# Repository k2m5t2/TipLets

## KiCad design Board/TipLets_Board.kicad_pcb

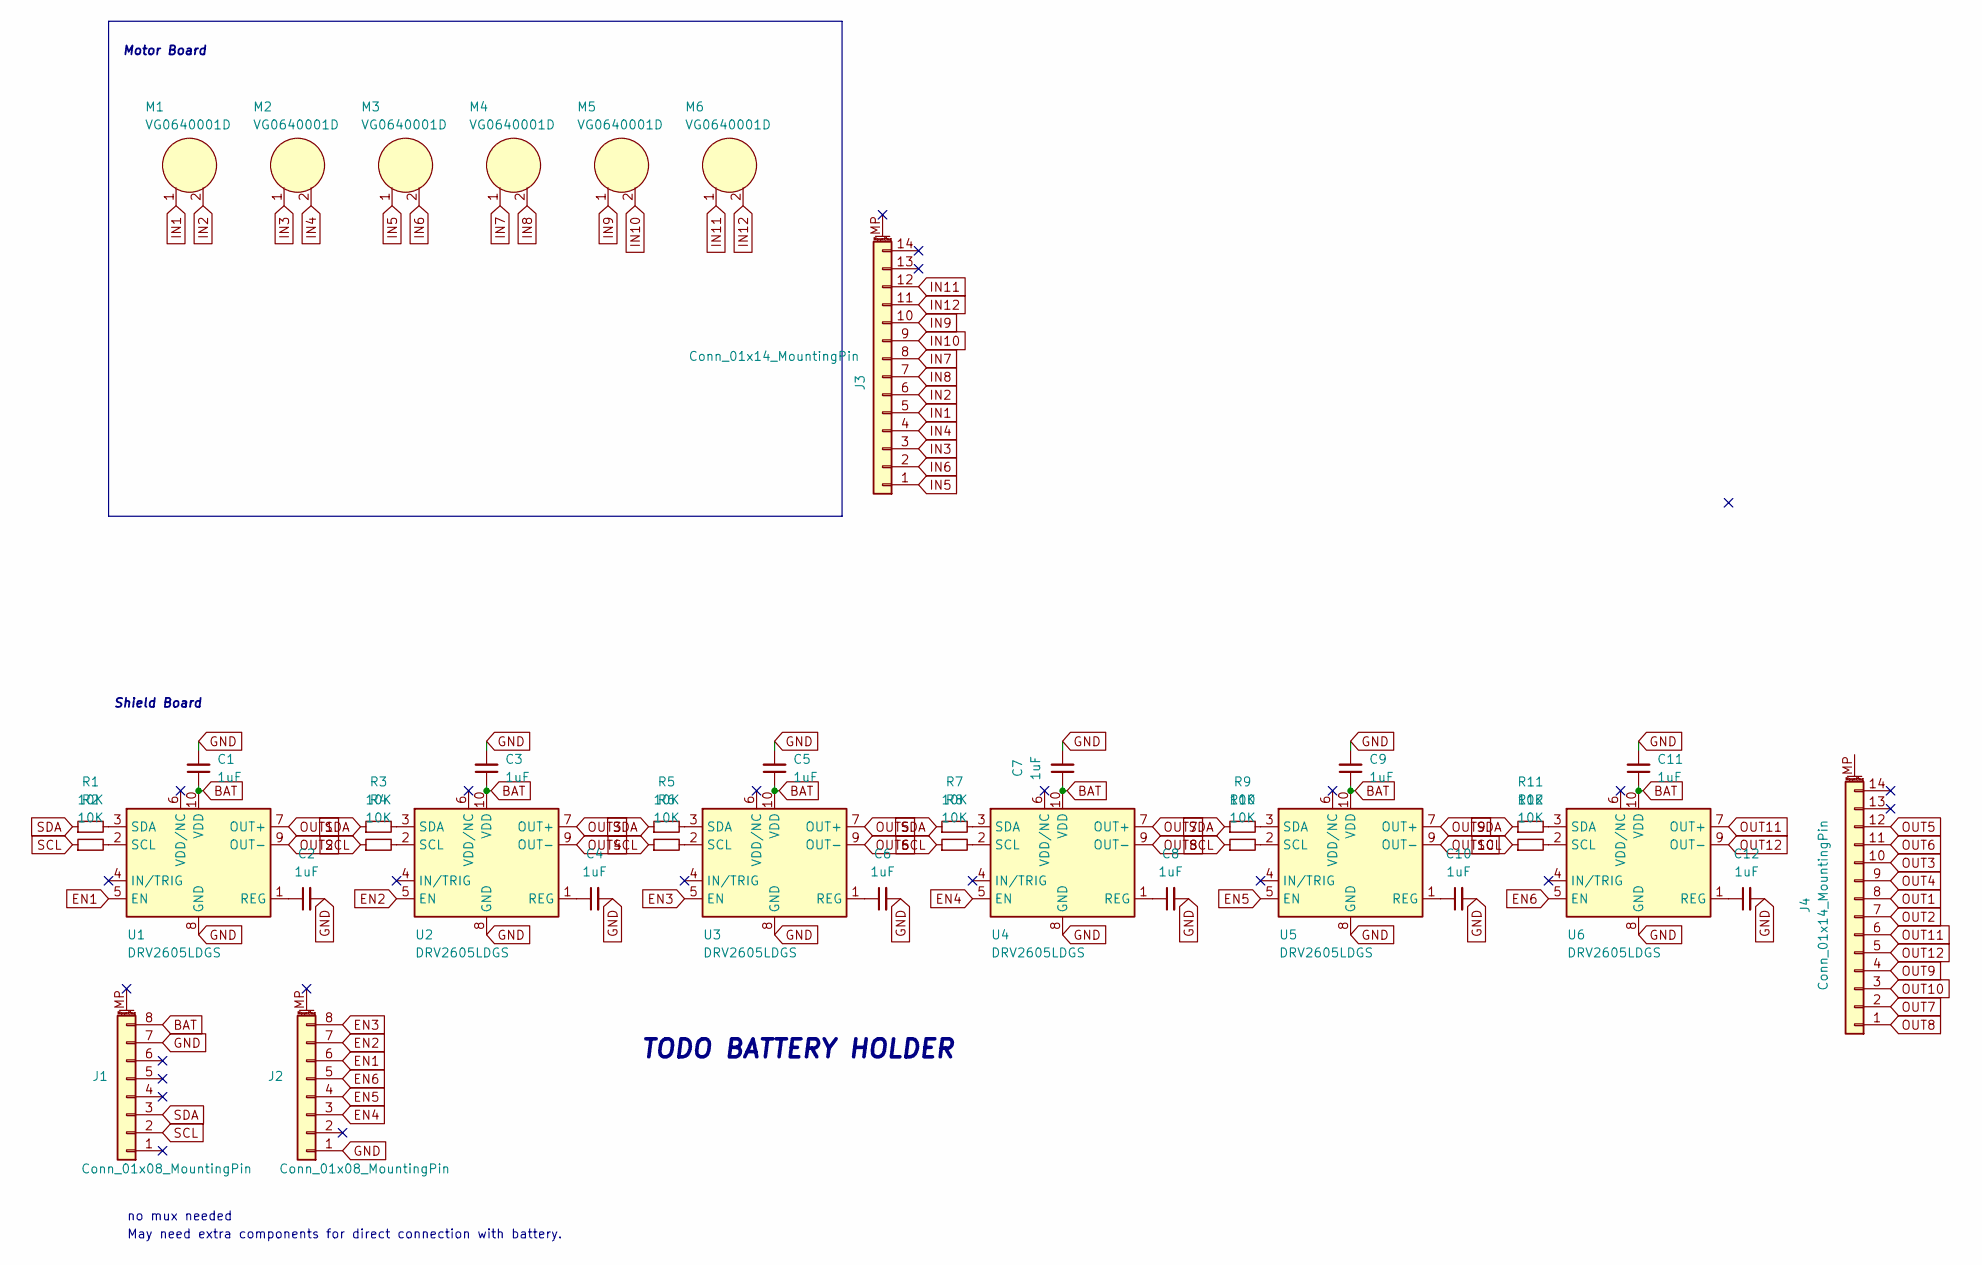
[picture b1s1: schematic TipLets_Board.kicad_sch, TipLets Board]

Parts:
C1, C2, C3, C4, C5, C6, C7, C8, C9, C10, C11, C12: 1uF; C_0402_1005Metric
J1, J2: Conn_01x08_MountingPin; PinHeader_1x08_P2.54mm_Vertical
J3, J4: Conn_01x14_MountingPin; PinHeader_2x07_P2.00mm_Vertical
M1, M2, M3, M4, M5, M6: VG0640001D
R1, R2, R3, R4, R5, R6, R7, R8, R9, R10, R11, R12: 10K; R_0402_1005Metric
U1, U2, U3, U4, U5, U6: DRV2605LDGS; VSSOP-10_3x3mm_P0.5mm

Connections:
BAT: C1.1, C3.1, C5.1, C7.1, C9.1, C11.1, J1.8, J2.2, U1.10 (VDD), U2.10 (VDD), U3.10 (VDD), U4.10 (VDD), U5.10 (VDD), U6.10 (VDD); also elsewhere on the board
EN1: J2.6, U1.5 (EN)
EN2: J2.7, U2.5 (EN)
EN3: J2.8, U3.5 (EN)
EN4: J2.3, U4.5 (EN)
EN5: J2.4, U5.5 (EN)
EN6: J2.5, U6.5 (EN)
GND: C1.2, C2.2, C3.2, C4.2, C5.2, C6.2, C7.2, C8.2, C9.2, C10.2, C11.2, C12.2, J1.7, J2.1, U1.8 (GND), U2.8 (GND), U3.8 (GND), U4.8 (GND), U5.8 (GND), U6.8 (GND); also elsewhere on the board
IN1: J3.5, M1.1
IN2: J3.6, M1.2
IN3: J3.3, M2.1
IN4: J3.4, M2.2
IN5: J3.1, M3.1
IN6: J3.2, M3.2
IN7: J3.8, M4.1
IN8: J3.7, M4.2
IN9: J3.10, M5.1
IN10: J3.9, M5.2
IN11: J3.12, M6.1
IN12: J3.11, M6.2
unnamed: C2.1, U1.1 (REG)
unnamed: C4.1, U2.1 (REG)
unnamed: C6.1, U3.1 (REG)
unnamed: C8.1, U4.1 (REG)
unnamed: C10.1, U5.1 (REG)
unnamed: C12.1, U6.1 (REG)
unnamed: R1.2, U1.3 (SDA)
unnamed: R2.2, U1.2 (SCL)
unnamed: R3.2, U2.3 (SDA)
unnamed: R4.2, U2.2 (SCL)
unnamed: R5.2, U3.3 (SDA)
unnamed: R6.2, U3.2 (SCL)
unnamed: R7.2, U4.3 (SDA)
unnamed: R8.2, U4.2 (SCL)
unnamed: R9.2, U5.3 (SDA)
unnamed: R10.2, U5.2 (SCL)
unnamed: R11.2, U6.3 (SDA)
unnamed: R12.2, U6.2 (SCL)
OUT1: J4.8, U1.7 (OUT+)
OUT2: J4.7, U1.9 (OUT-)
OUT3: J4.10, U2.7 (OUT+)
OUT4: J4.9, U2.9 (OUT-)
OUT5: J4.12, U3.7 (OUT+)
OUT6: J4.11, U3.9 (OUT-)
OUT7: J4.2, U4.7 (OUT+)
OUT8: J4.1, U4.9 (OUT-)
OUT9: J4.4, U5.7 (OUT+)
OUT10: J4.3, U5.9 (OUT-)
OUT11: J4.6, U6.7 (OUT+)
OUT12: J4.5, U6.9 (OUT-)
SCL: J1.2, R2.1, R4.1, R6.1, R8.1, R10.1, R12.1
SDA: J1.3, R1.1, R3.1, R5.1, R7.1, R9.1, R11.1

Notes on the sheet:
Motor Board
TODO BATTERY HOLDER
May need extra components for direct connection with battery.
Shield Board
no mux needed

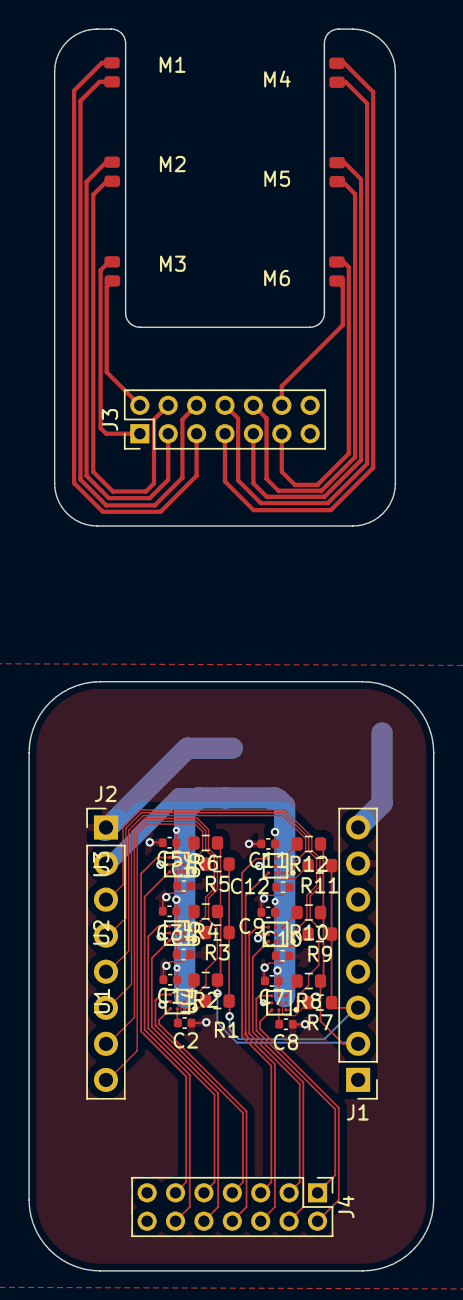
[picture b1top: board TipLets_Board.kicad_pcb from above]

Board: 2 copper layers, 28.5 x 87.5 mm, 41 parts (1 on the bottom side), 52 nets.

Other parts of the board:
B1: SMD_Battery_Clip; BK5009

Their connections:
BAT: B1.1 (+), B1.2 (+); also elsewhere on the board
GND: B1.3; also elsewhere on the board

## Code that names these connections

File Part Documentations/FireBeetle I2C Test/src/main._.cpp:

/*
    Basic Pin setup:
    ------------                                  ---u----
    ARDUINO   13|-> SCLK (pin 25)           OUT1 |1     28| OUT channel 0
              12|                           OUT2 |2     27|-> GND (VPRG)
              11|-> SIN (pin 26)            OUT3 |3     26|-> SIN (pin 11)
              10|-> BLANK (pin 23)          OUT4 |4     25|-> SCLK (pin 13)
               9|-> XLAT (pin 24)             .  |5     24|-> XLAT (pin 9)
               8|                             .  |6     23|-> BLANK (pin 10)
               7|                             .  |7     22|-> GND
               6|                             .  |8     21|-> VCC (+5V)
               5|                             .  |9     20|-> 2K Resistor -> GND
               4|                             .  |10    19|-> +5V (DCPRG)
               3|-> GSCLK (pin 18)            .  |11    18|-> GSCLK (pin 3)
               2|                             .  |12    17|-> SOUT
               1|                             .  |13    16|-> XERR
               0|                           OUT14|14    15| OUT channel 15
    ------------                                  --------

    -  Put the longer leg (anode) of the LEDs in the +5V and the shorter leg
         (cathode) in OUT(0-15).
    -  +5V from Arduino -> TLC pin 21 and 19     (VCC and DCPRG)
    -  GND from Arduino -> TLC pin 22 and 27     (GND and VPRG)
    -  digital 3        -> TLC pin 18            (GSCLK)
    -  digital 9        -> TLC pin 24            (XLAT)
    -  digital 10       -> TLC pin 23            (BLANK)
    -  digital 11       -> TLC pin 26            (SIN)
    -  digital 13       -> TLC pin 25            (SCLK)
    -  The 2K resistor between TLC pin 20 and GND will let ~20mA through each
       LED.  To be precise, it's I = 39.06 / R (in ohms).  This doesn't depend
       on the LED driving voltage.
    - (Optional): put a pull-up resistor (~10k) between +5V and BLANK so that
                  all the LEDs will turn off when the Arduino is reset.

    If you are daisy-chaining more than one TLC, connect the SOUT of the first
    TLC to the SIN of the next.  All the other pins should just be connected
    together:
        BLANK on Arduino -> BLANK of TLC1 -> BLANK of TLC2 -> ...
        XLAT on Arduino  -> XLAT of TLC1  -> XLAT of TLC2  -> ...
    The one exception is that each TLC needs it's own resistor between pin 20
    and GND.

    This library uses the PWM output ability of digital pins 3, 9, 10, and 11.
    Do not use analogWrite(...) on these pins.

    This sketch does the Knight Rider strobe across a line of LEDs.

    Alex Leone <acleone ~AT~ gmail.com>, 2009-02-03 */

#include "Tlc5940.h"

void setup()
{
  /* Call Tlc.init() to setup the tlc.
     You can optionally pass an initial PWM value (0 - 4095) for all channels.*/
  Tlc.init();
}

/* This loop will create a Knight Rider-like effect if you have LEDs plugged
   into all the TLC outputs.  NUM_TLCS is defined in "tlc_config.h" in the
   library folder.  After editing tlc_config.h for your setup, delete the
   Tlc5940.o file to save the changes. */

void loop()
{
  int direction = 1;
  for (int channel = 0; channel < NUM_TLCS * 16; channel += direction) {

    /* Tlc.clear() sets all the grayscale values to zero, but does not send
       them to the TLCs.  To actually send the data, call Tlc.update() */
    Tlc.clear();

    /* Tlc.set(channel (0-15), value (0-4095)) sets the grayscale value for
       one channel (15 is OUT15 on the first TLC, if multiple TLCs are daisy-
       chained, then channel = 16 would be OUT0 of the second TLC, etc.).

       value goes from off (0) to always on (4095).

       Like Tlc.clear(), this function only sets up the data, Tlc.update()
       will send the data. */
    if (channel == 0) {
      direction = 1;
    } else {
      Tlc.set(channel - 1, 1000);
    }
    Tlc.set(channel, 4095);
    if (channel != NUM_TLCS * 16 - 1) {
      Tlc.set(channel + 1, 1000);
    } else {
      direction = -1;
    }

    /* Tlc.update() sends the data to the TLCs.  This is when the LEDs will
       actually change. */
    Tlc.update();

    delay(75);
  }

}

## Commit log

2023-09-03 Folder Restructuring
2023-09-03 Texture Bake Practice 1
